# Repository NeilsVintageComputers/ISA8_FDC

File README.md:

# ISA8_FDC

These FDCs are based on the Sergey Monster FDC, they use the Sergey FDC Bios V2.2, at the time of writing this was up to version 2.6 which should also work.

V1.0 is a 4-way FDC and has a external 37-pin connector option for the second pair of drives.

V2.0 supercedes V1.0, it is a 4-way FDC that has a internal PCB edge connector option for the first pair of drives and a external 37-pin connector option for the second pair of drives.

V1.0

V2.0

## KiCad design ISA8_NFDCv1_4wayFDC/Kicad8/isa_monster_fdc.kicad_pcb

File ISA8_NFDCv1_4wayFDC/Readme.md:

# NFDC V1.0 ISA8 FDC

This FDC is based on the Sergey Monster FDC, and uses the Sergey FDC Bios.

I have cut it down to a 4-way controller and added a external 37-pin connector using standard IBM pin connection that can be used for the second pair of drives.

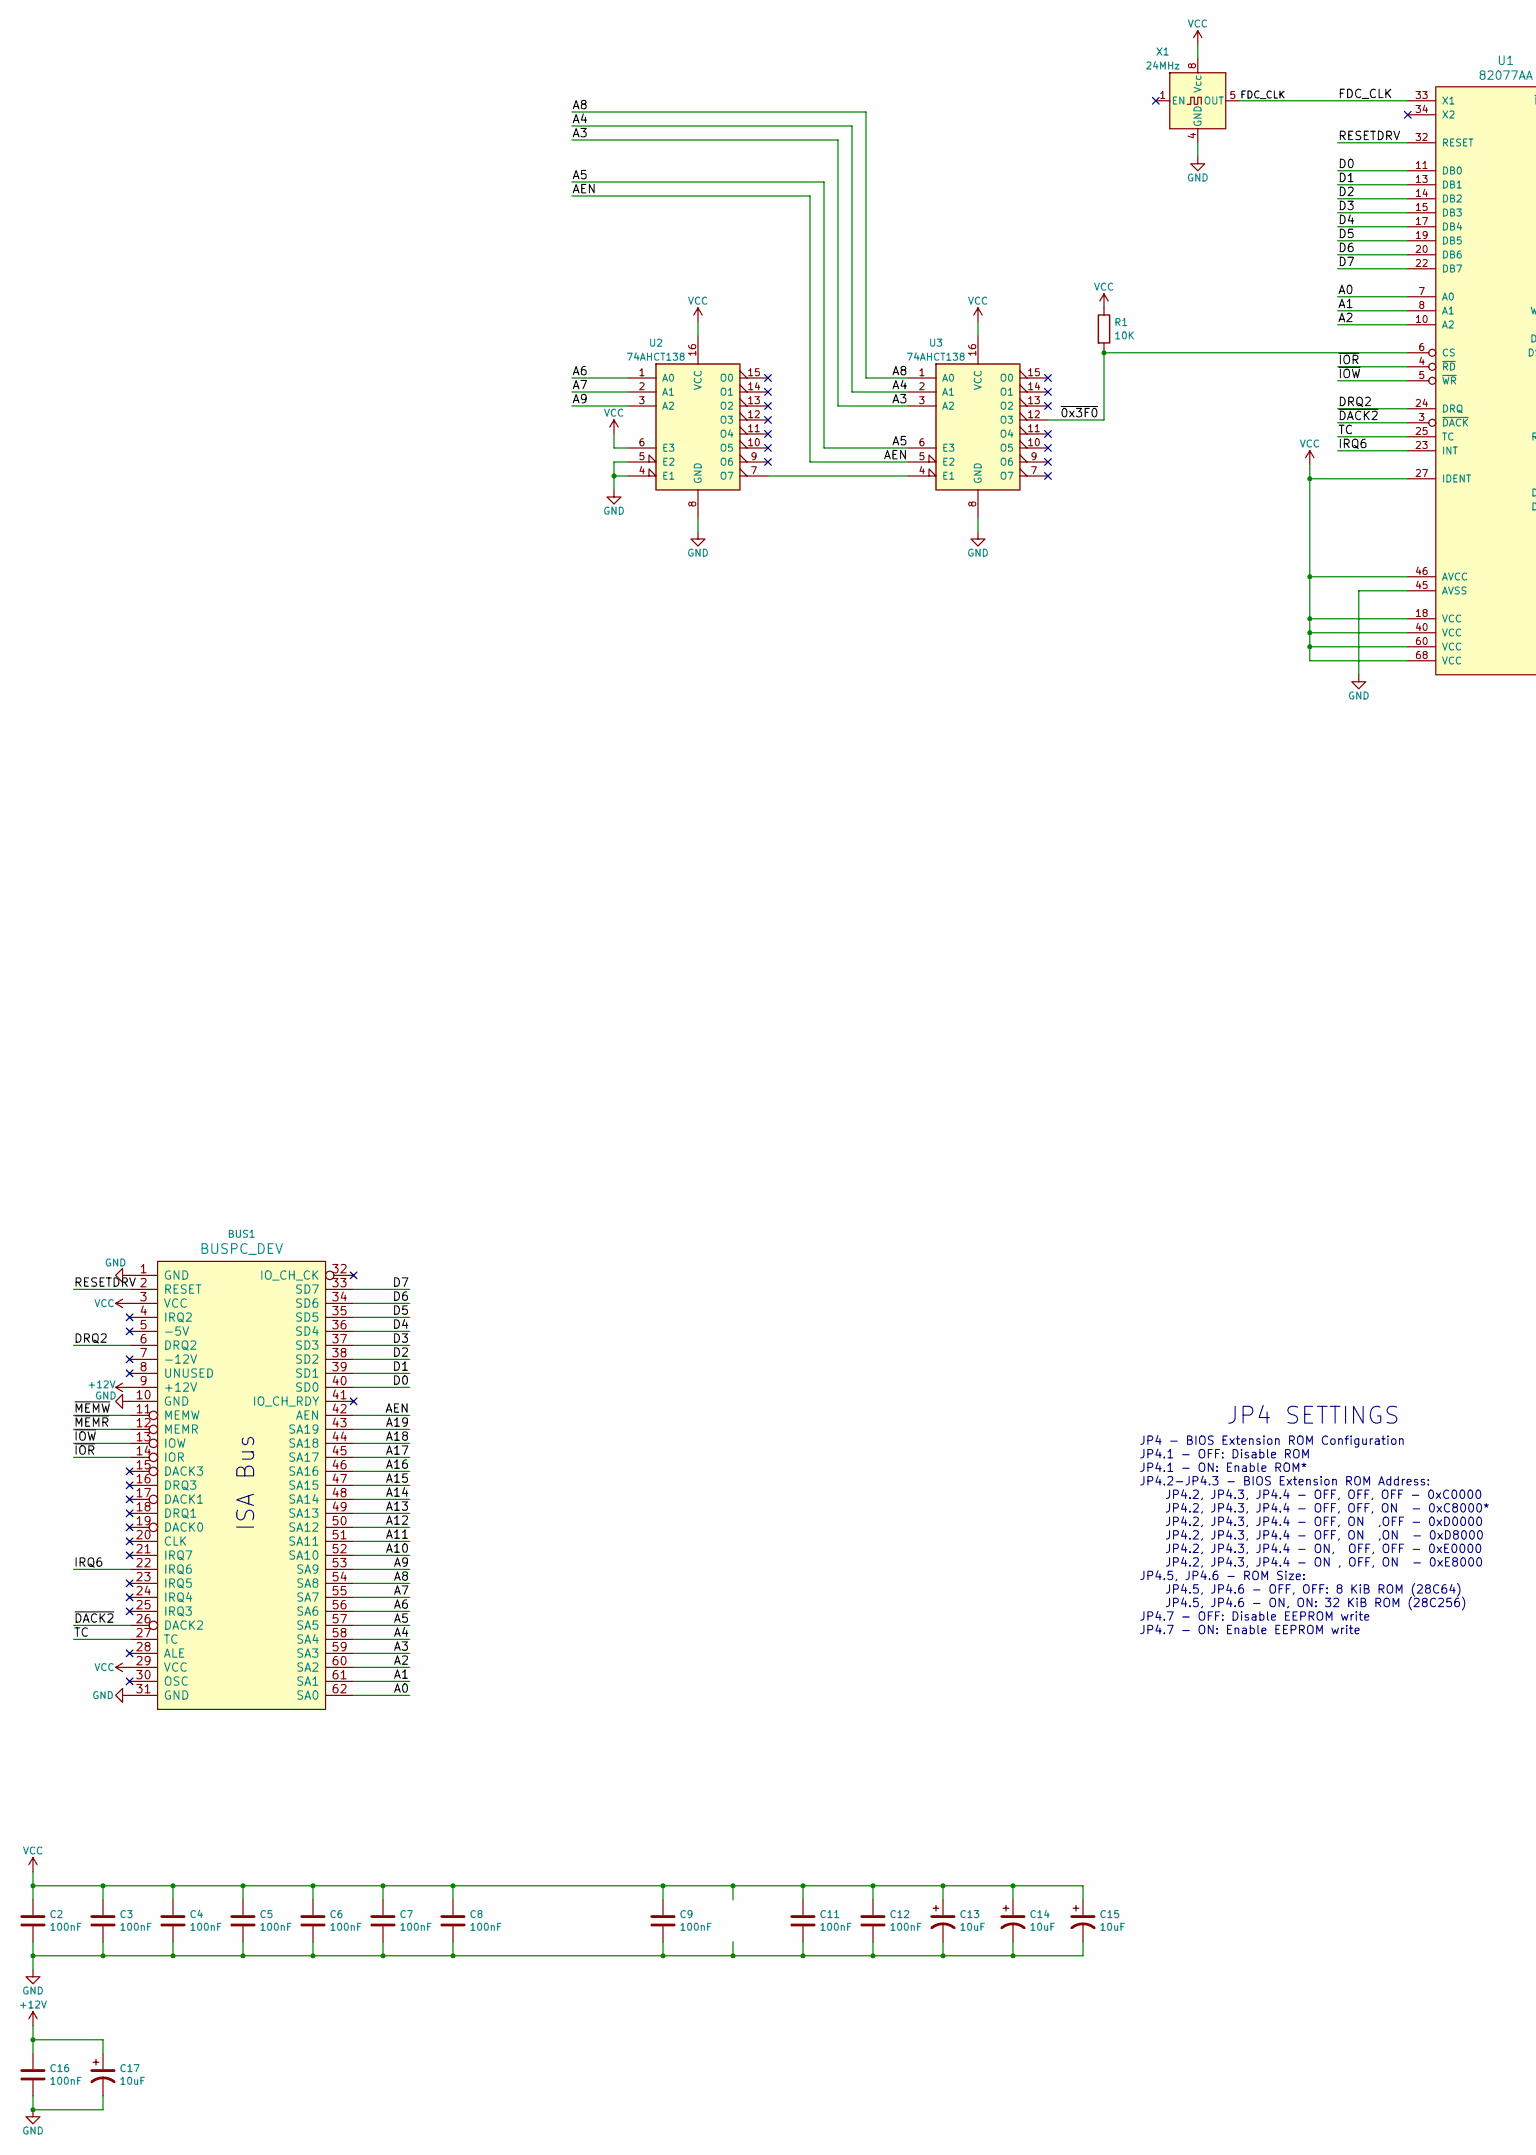
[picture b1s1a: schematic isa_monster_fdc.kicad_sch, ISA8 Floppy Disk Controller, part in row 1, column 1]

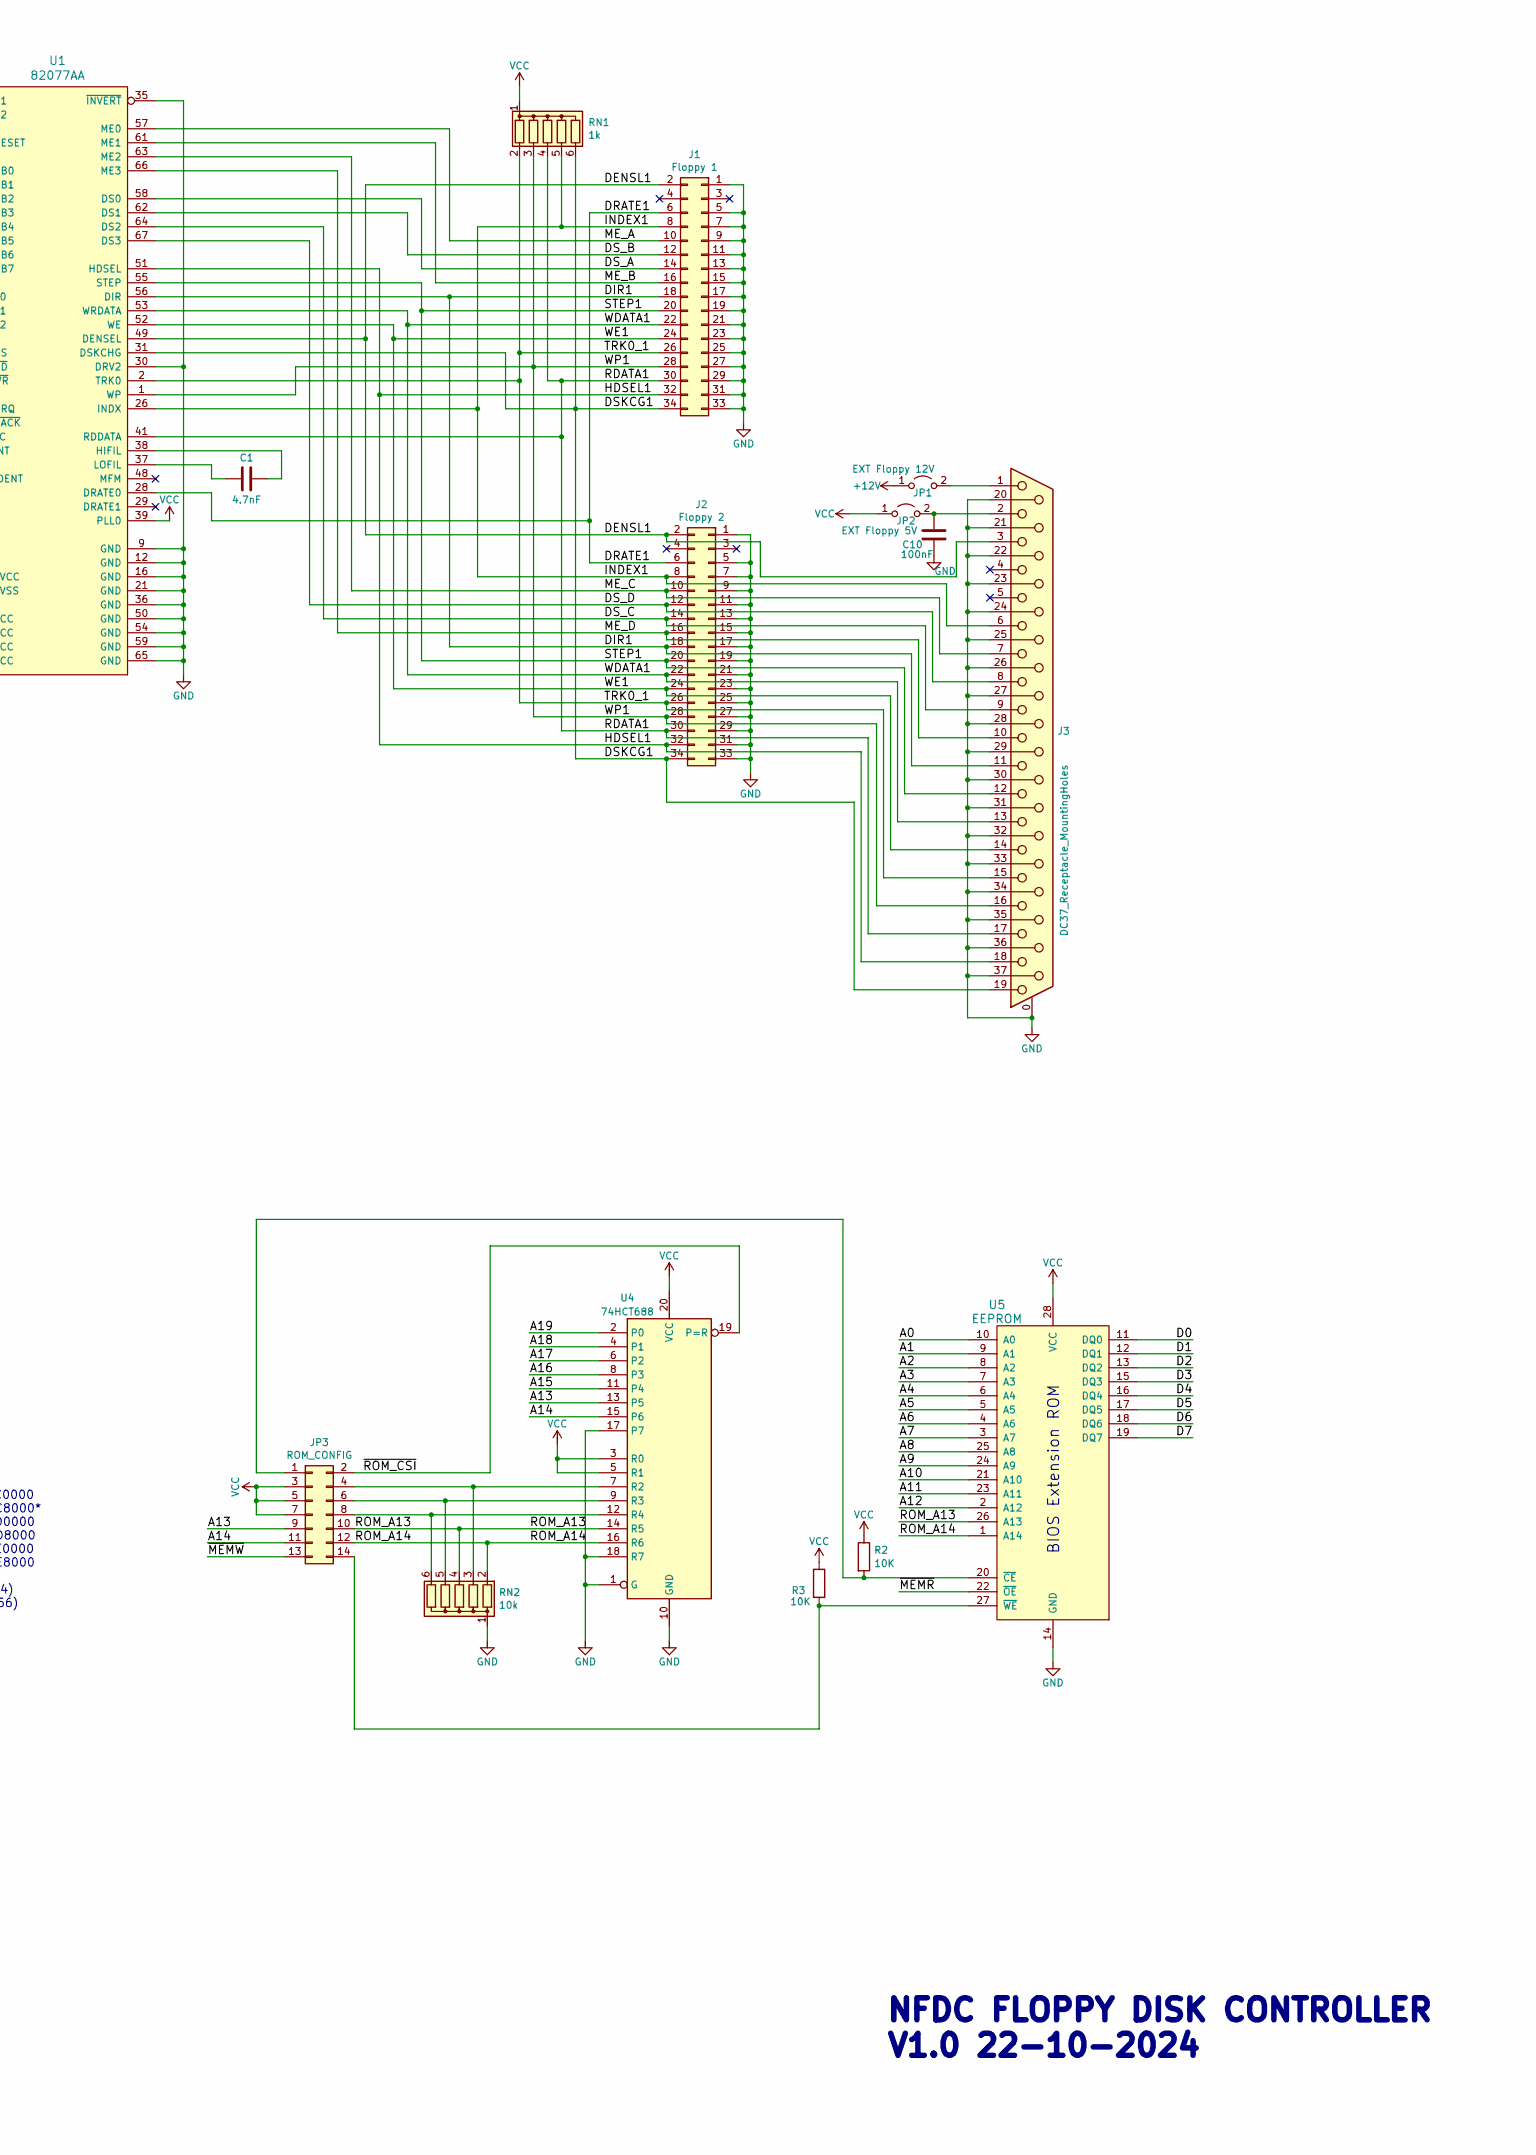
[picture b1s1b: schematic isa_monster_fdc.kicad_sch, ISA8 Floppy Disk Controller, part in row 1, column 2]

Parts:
BUS1: BUSPC_DEV; Conn_Edge_PCB_ISA8
C1: 4.7nF; C_Disc_D3.0mm_W2.0mm_P2.50mm
C2, C3, C4, C5, C6, C7, C8, C9, C10, C11, C12, C16: 100nF; C_Disc_D8.0mm_W5.0mm_P5.00mm
C13, C14, C15, C17: 10uF; CP_Radial_D8.0mm_P2.50mm
J1: Floppy 1; PinHeader_2x17_P2.54mm_Vertical
J2: Floppy 2; PinHeader_2x17_P2.54mm_Vertical
J3: DC37_Receptacle_MountingHoles; DSUB-37_Female_Horizontal_P2.77x2.84mm_EdgePinOffset7.70mm_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
JP1: EXT Floppy 12V; SolderJumper-2_P1.3mm_Open_RoundedPad1.0x1.5mm
JP2: EXT Floppy 5V; SolderJumper-2_P1.3mm_Open_RoundedPad1.0x1.5mm
JP3: ROM_CONFIG; PinHeader_2x07_P2.54mm_Vertical
R1, R2, R3: 10K; R_Axial_DIN0411_L9.9mm_D3.6mm_P12.70mm_Horizontal
RN1: 1k; R_Array_SIP6
RN2: 10k; R_Array_SIP6
U1: 82077AA; PLCC-68_THT-Socket
U2, U3: 74AHCT138; DIP-16_W7.62mm_LongPads
U4: 74HCT688; DIP-20_W7.62mm_LongPads
U5: EEPROM; DIP-28_W15.24mm_Socket_LongPads
X1: 24MHz; Oscillator_DIP-8

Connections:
+12V: BUS1.9 (+12V), C16.1, C17.1, JP1.1 (A)
/A0: BUS1.62 (SA0), U1.7 (A0), U5.10 (A0)
/A1: BUS1.61 (SA1), U1.8 (A1), U5.9 (A1)
/A2: BUS1.60 (SA2), U1.10 (A2), U5.8 (A2)
/A3: BUS1.59 (SA3), U3.3 (A2), U5.7 (A3)
/A4: BUS1.58 (SA4), U3.2 (A1), U5.6 (A4)
/A5: BUS1.57 (SA5), U3.6 (E3), U5.5 (A5)
/A6: BUS1.56 (SA6), U2.1 (A0), U5.4 (A6)
/A7: BUS1.55 (SA7), U2.2 (A1), U5.3 (A7)
/A8: BUS1.54 (SA8), U3.1 (A0), U5.25 (A8)
/A9: BUS1.53 (SA9), U2.3 (A2), U5.24 (A9)
/A10: BUS1.52 (SA10), U5.21 (A10)
/A11: BUS1.51 (SA11), U5.23 (A11)
/A12: BUS1.50 (SA12), U5.2 (A12)
/A13: BUS1.49 (SA13), JP3.9, U4.13 (P5)
/A14: BUS1.48 (SA14), JP3.11, U4.15 (P6)
/A15: BUS1.47 (SA15), U4.11 (P4)
/A16: BUS1.46 (SA16), U4.8 (P3)
/A17: BUS1.45 (SA17), U4.6 (P2)
/A18: BUS1.44 (SA18), U4.4 (P1)
/A19: BUS1.43 (SA19), U4.2 (P0)
/AEN: BUS1.42 (AEN), U3.5 (E2)
/D0: BUS1.40 (SD0), U1.11 (DB0), U5.11 (DQ0)
/D1: BUS1.39 (SD1), U1.13 (DB1), U5.12 (DQ1)
/D2: BUS1.38 (SD2), U1.14 (DB2), U5.13 (DQ2)
/D3: BUS1.37 (SD3), U1.15 (DB3), U5.15 (DQ3)
/D4: BUS1.36 (SD4), U1.17 (DB4), U5.16 (DQ4)
/D5: BUS1.35 (SD5), U1.19 (DB5), U5.17 (DQ5)
/D6: BUS1.34 (SD6), U1.20 (DB6), U5.18 (DQ6)
/D7: BUS1.33 (SD7), U1.22 (DB7), U5.19 (DQ7)
/DENSL1: J1.2, J2.2, J3.3, U1.49 (DENSEL)
/DIR1: J1.18, J2.18, J3.11, U1.56 (DIR)
/DRATE1: J1.6, J2.6, U1.28 (DRATE0)
/DRQ2: BUS1.6 (DRQ2), U1.24 (DRQ)
/DSKCG1: J1.34, J2.34, J3.19, RN1.6 (R5), U1.31 (DSKCHG)
/DS_A: J1.14, U1.58 (DS0)
/DS_B: J1.12, U1.62 (DS1)
/DS_C: J2.14, J3.9, U1.64 (DS2)
/DS_D: J2.12, J3.8, U1.67 (DS3)
/FDC_CLK: U1.33 (X1), X1.5 (OUT)
/HDSEL1: J1.32, J2.32, J3.18, U1.51 (HDSEL)
/INDEX1: J1.8, J2.8, J3.6, RN1.5 (R4), U1.26 (INDX)
/IRQ6: BUS1.22 (IRQ6), U1.23 (INT)
/ME_A: J1.10, U1.57 (ME0)
/ME_B: J1.16, U1.61 (ME1)
/ME_C: J2.10, J3.7, U1.63 (ME2)
/ME_D: J2.16, J3.10, U1.66 (ME3)
/RDATA1: J1.30, J2.30, J3.17, RN1.4 (R3), U1.41 (RDDATA)
/RESETDRV: BUS1.2 (RESET), U1.32 (RESET)
/ROM_A13: JP3.10, RN2.4 (R3), U4.14 (R5), U5.26 (A13)
/ROM_A14: JP3.12, RN2.2 (R1), U4.16 (R6), U5.1 (A14)
/STEP1: J1.20, J2.20, J3.12, U1.55 (STEP)
/TC: BUS1.27 (TC), U1.25 (TC)
/TRK0_1: J1.26, J2.26, J3.15, RN1.2 (R1), U1.2 (TRK0)
/WDATA1: J1.22, J2.22, J3.13, U1.53 (WRDATA)
/WE1: J1.24, J2.24, J3.14, U1.52 (WE)
/WP1: J1.28, J2.28, J3.16, RN1.3 (R2), U1.1 (WP)
/~0x3F0: R1.2, U1.6 (CS), U3.12 (O3)
/~DACK2: BUS1.26 (DACK2), U1.3 (~DACK)
/~IOR: BUS1.14 (IOR), U1.4 (~RD)
/~IOW: BUS1.13 (IOW), U1.5 (~WR)
/~MEMR: BUS1.12 (MEMR), U5.22 (~OE)
/~MEMW: BUS1.11 (MEMW), JP3.13
/~ROM_CSI: JP3.2, U4.19 (P=R)
GND: BUS1.1 (GND), BUS1.10 (GND), BUS1.31 (GND), C2.2, C3.2, C4.2, C5.2, C6.2, C7.2, C8.2, C9.2, C10.2, C11.2, C12.2, C13.2, C14.2, C15.2, C16.2, C17.2, J1.1, J1.5, J1.7, J1.9, J1.11, J1.13, J1.15, J1.17, J1.19, J1.21, J1.23, J1.25, J1.27, J1.29, J1.31, J1.33, J2.1, J2.5, J2.7, J2.9, J2.11, J2.13, J2.15, J2.17, J2.19, J2.21, J2.23, J2.25, J2.27, J2.29, J2.31, J2.33, J3.0 (PAD), J3.20, J3.21, J3.22, J3.23, J3.24, J3.25, J3.26, J3.27, J3.28, J3.29, J3.30, J3.31, J3.32, J3.33, J3.34, J3.35, J3.36, J3.37, RN2.1 (common), U1.9 (GND), U1.12 (GND), U1.16 (GND), U1.21 (GND), U1.30 (DRV2), U1.35 (~INVERT), U1.36 (GND), U1.45 (AVSS), U1.50 (GND), U1.54 (GND), U1.59 (GND), U1.65 (GND), U2.4 (E1), U2.5 (E2), U2.8 (GND), U3.8 (GND), U4.1 (G), U4.10 (GND), U4.17 (P7), U4.18 (R7), U5.14 (GND), X1.4 (GND)
unnamed: J3.1, JP1.2 (B)
unnamed: C10.1, J3.2, JP2.2 (B)
unnamed: JP3.1, R2.2, U5.20 (~CE)
unnamed: JP3.4, RN2.3 (R2), U4.7 (R2)
unnamed: JP3.6, RN2.5 (R4), U4.9 (R3)
unnamed: JP3.8, RN2.6 (R5), U4.12 (R4)
unnamed: JP3.14, R3.2, U5.27 (~WE)
unnamed: C1.1, U1.38 (HIFIL)
unnamed: C1.2, U1.37 (LOFIL)
unnamed: U2.7 (O7), U3.4 (E1)
VCC: BUS1.3 (VCC), BUS1.29 (VCC), C2.1, C3.1, C4.1, C5.1, C6.1, C7.1, C8.1, C9.1, C11.1, C12.1, C13.1, C14.1, C15.1, JP2.1 (A), JP3.3, JP3.5, JP3.7, R1.1, R2.1, R3.1, RN1.1 (common), U1.18 (VCC), U1.27 (IDENT), U1.39 (PLL0), U1.40 (VCC), U1.46 (AVCC), U1.60 (VCC), U1.68 (VCC), U2.6 (E3), U2.16 (VCC), U3.16 (VCC), U4.3 (R0), U4.5 (R1), U4.20 (VCC), U5.28 (VCC), X1.8 (Vcc)

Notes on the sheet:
JP4 - BIOS Extension ROM Configuration JP4.1 - OFF: Disable ROM JP4.1 - ON: Enable ROM* JP4.2-JP4.3 - BIOS Extension ROM Address: JP4.2, JP4.3, JP4.4 - OFF, OFF, OFF - 0xC0000 JP4.2, JP4.3, JP4.4 - OFF, OFF, ON - 0xC8000* JP4.2, JP4.3, JP4.4 - OFF, ON ,OFF - 0xD0000 JP4.2, JP4.3, JP4.4 - OFF, ON ,O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
BIOS Extension ROM
NFDC FLOPPY DISK CONTROLLER V1.0 22-10-2024
JP4 SETTINGS
ISA Bus

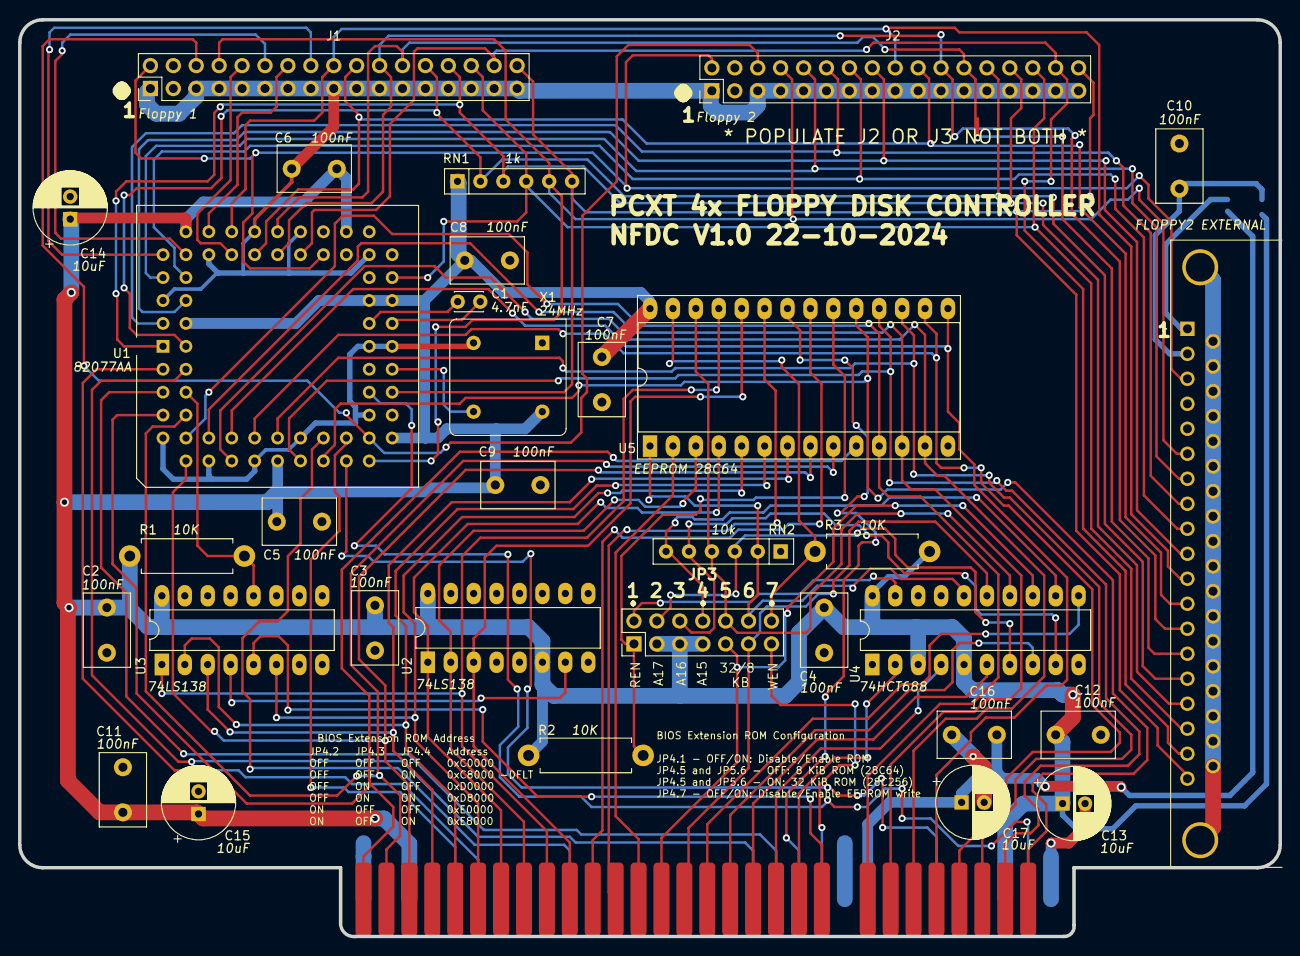
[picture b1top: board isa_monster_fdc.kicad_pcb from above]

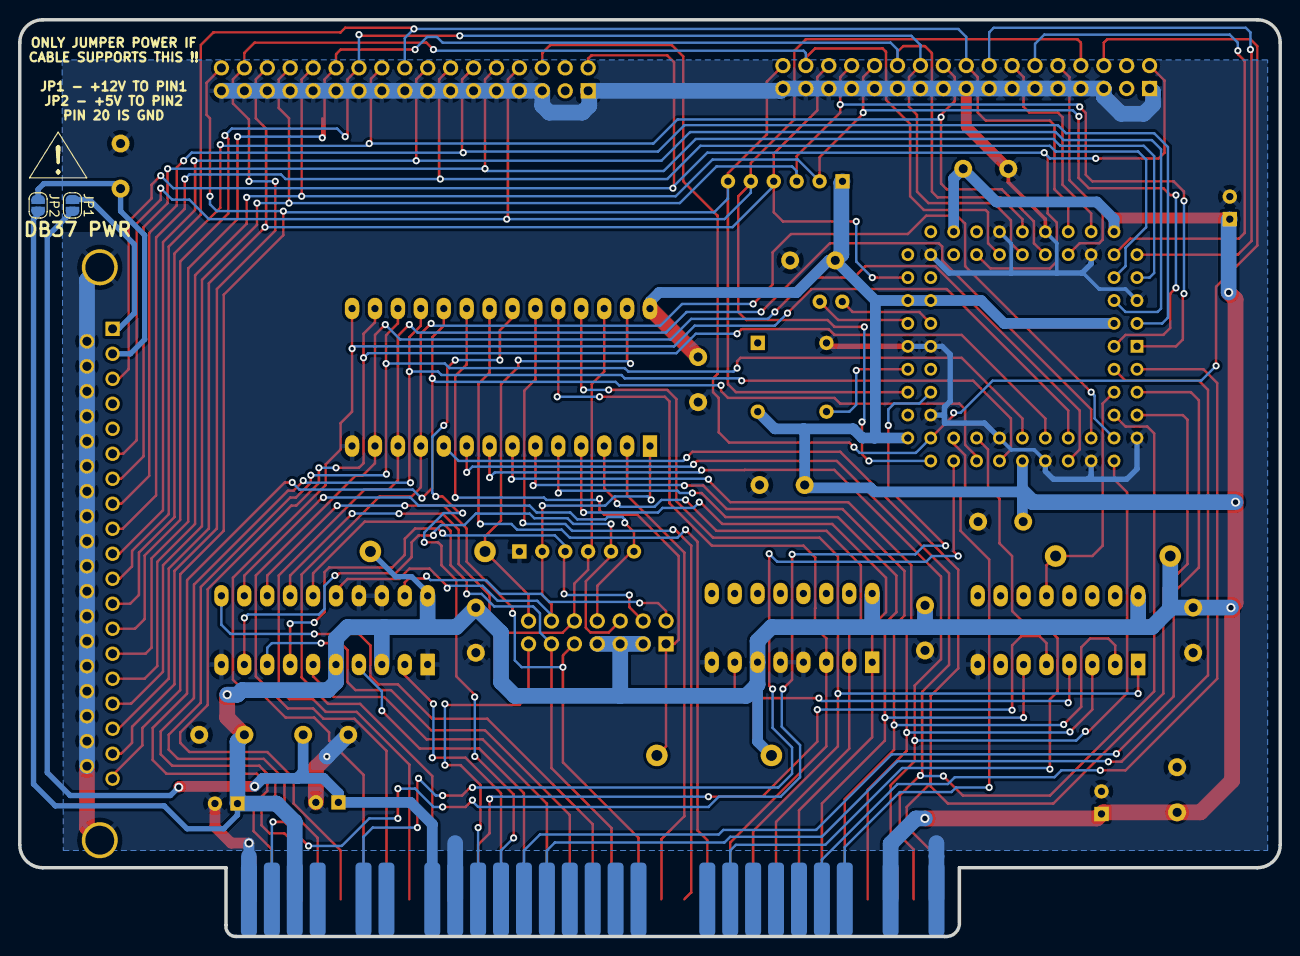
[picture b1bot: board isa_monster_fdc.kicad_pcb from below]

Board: 2 copper layers, 139.7 x 101.6 mm, 35 parts (2 on the bottom side), 76 nets.

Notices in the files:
ISA8_NFDCv1_4wayFDC/Kicad8/isa_monster_fdc.kicad_pcb:
Licensed under CERN-OHL-S: https://cern-ohl.web.cern.ch
